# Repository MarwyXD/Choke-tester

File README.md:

# Choke-tester

# This choke tester i built is from one of my older magazine called "Amatérské Rádio", it´s full of usefull knowledge and nice schematics like this.

# It nicely show where the so called "overshoot point" is (bod přesycení), if you have an osciloskope with 2 chanels you can nicely show the 2 characteristics.

# The first is square wave that creates 555 timer circuit, if we utilize lower frequency we wont be able to properly test the overshoot point, but if we will slowly rise this frequency we will see the rising satiating current to the coil, at some point the current must stop rising (due to the overshoot point), and we will see at wich frequency it is, so we will now know at wich point is our maximum frequency of the coil and we will not unnecesary supply current.

# Schematic of the project is available to all of you (as well as the rest of the zip file), and if you want you can create your own better schematic/PCB.

# All necessary part you will find in the eagle file.

# Thank you.

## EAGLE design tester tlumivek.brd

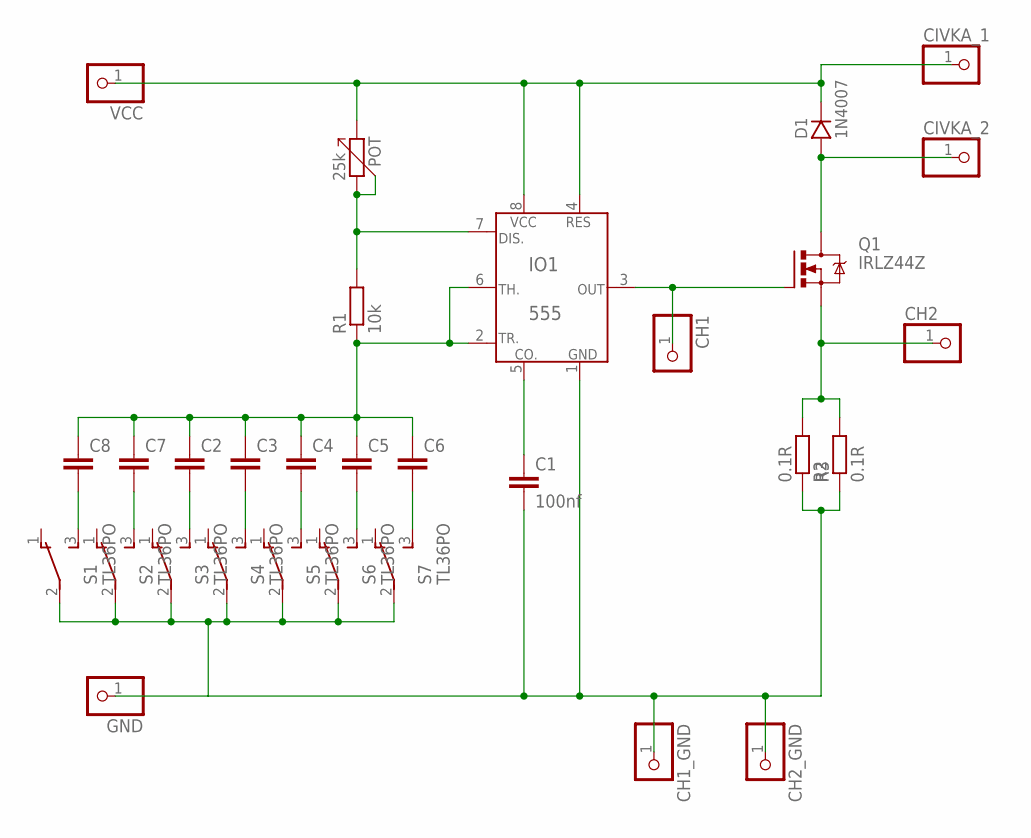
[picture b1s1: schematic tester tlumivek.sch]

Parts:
C1: 100nf; C075-042X103
C2, C3, C4, C5, C6, C7, C8: C-EU075-042X103; C075-042X103
CH1, CH1_GND, CH2, CH2_GND: PINHD-1X1; 1X01
CIVKA_1, CIVKA_2: PINHD-1X1; 1X01
D1: 1N4007; DO41
GND: PINHD-1X1; 1X01
IO1: 555; DIL8
POT: 25k; PC16ML
Q1: IRLZ44Z; TO220BH
R1: 10k; 0207/10
R2, R3: 0.1R; 0617/17
S1, S2, S3, S4, S5, S6, S7: TL36PO; TL3XPO
VCC: PINHD-1X1; 1X01

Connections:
unnamed: CIVKA_1.1, D1.K, IO1.4 (RES), IO1.8 (VCC), POT.1, VCC.1
unnamed: C1.1, IO1.5 (CO.)
unnamed: IO1.7 (DIS.), POT.2, POT.3, R1.2
unnamed: C8.2, S1.3 (S)
unnamed: CH1.1, IO1.3 (OUT), Q1.G
unnamed: CIVKA_2.1, D1.A, Q1.D
unnamed: CH2.1, Q1.S, R2.2, R3.2
unnamed: C7.2, S2.3 (S)
unnamed: C1.2, CH1_GND.1, CH2_GND.1, GND.1, IO1.1 (GND), R2.1, R3.1, S1.2, S2.2, S3.2, S4.2, S5.2, S6.2, S7.2
unnamed: C2.2, S3.3 (S)
unnamed: C3.2, S4.3 (S)
unnamed: C4.2, S5.3 (S)
unnamed: C5.2, S6.3 (S)
unnamed: C6.2, S7.3 (S)
unnamed: C2.1, C3.1, C4.1, C5.1, C6.1, C7.1, C8.1, IO1.2 (TR.), IO1.6 (TH.), R1.1

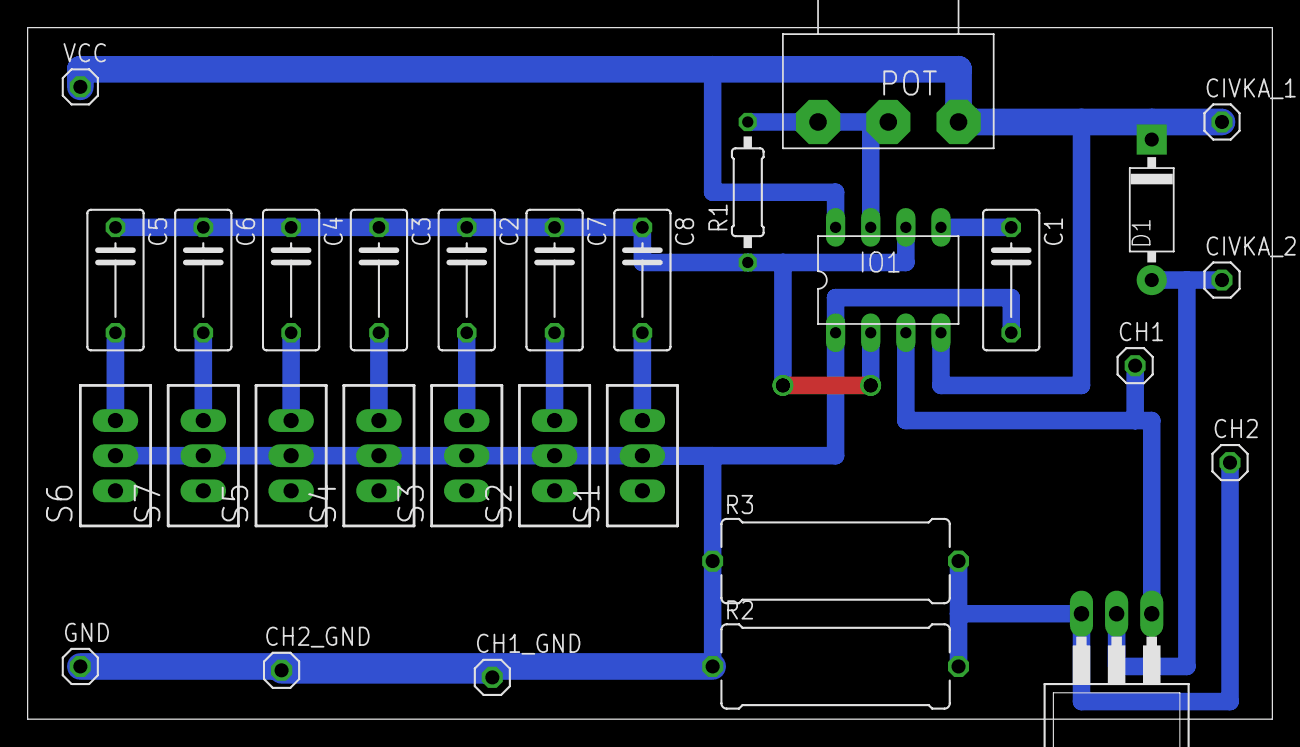
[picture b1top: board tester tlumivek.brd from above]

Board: 2 copper layers, 90.0 x 50.0 mm, 30 parts (0 on the bottom side), 15 nets.

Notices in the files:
parts and their libraries:
Copyright (C) PaJa 2001-2014
